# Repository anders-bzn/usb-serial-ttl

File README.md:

# usb-serial-ttl
Isolated USB to serial adapter, TTL 1.8/3.3V level. The IO voltage needs to be
supplied from the host.

Uses KiCad 8.0 and [kicad-jlcpcb-tools](https://github.com/Bouni/kicad-jlcpcb-tool3.3Vs)
plugin for creating fabrication files.

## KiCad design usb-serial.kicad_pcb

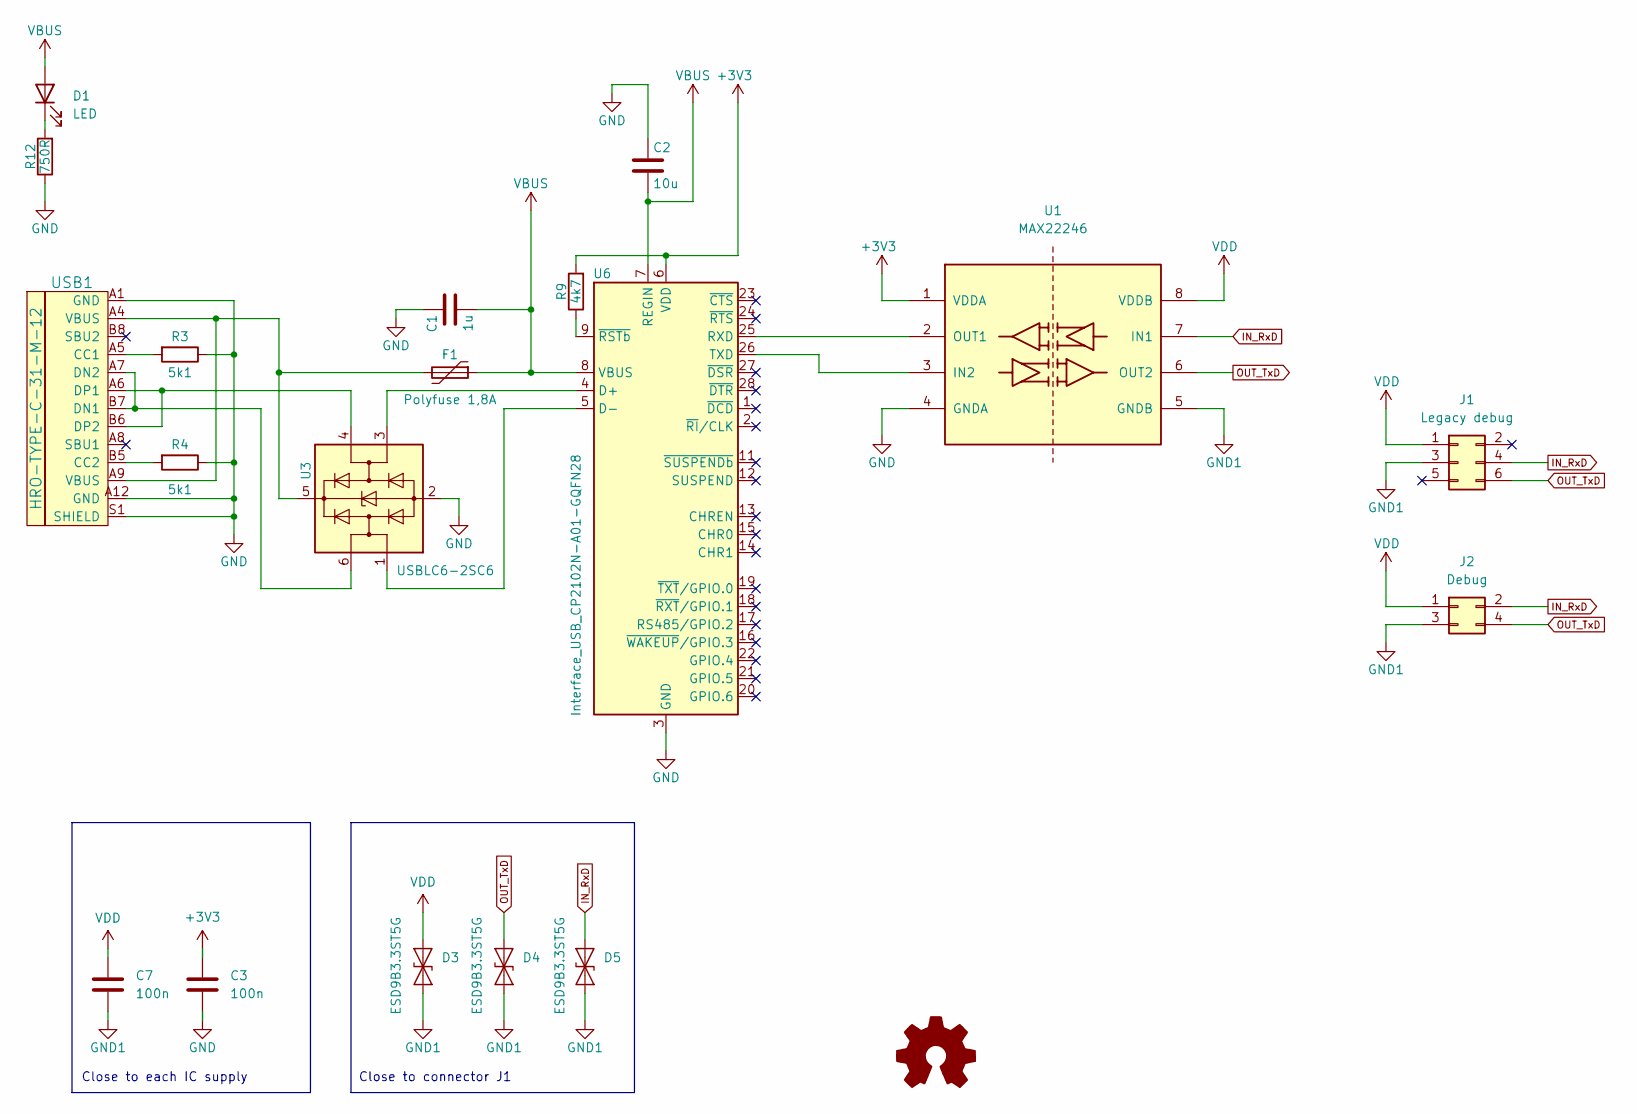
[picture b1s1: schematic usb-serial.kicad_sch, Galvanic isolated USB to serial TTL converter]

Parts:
C1: 1u; C_0805_2012Metric
C2: 10u; C_0805_2012Metric
C3, C7: 100n; C_0402_1005Metric
D1: LED; LED_0805_2012Metric
D3, D4, D5: ESD9B3.3ST5G; D_SOD-923
F1: Polyfuse 1,8A; Fuse_1206_3216Metric
J1: Legacy debug; PinHeader_2x03_P2.00mm_Vertical_SMD
J2: Debug; JST_PH_S4B-PH-SM4-TB_1x04-1MP_P2.00mm_Horizontal
R3, R4: 5k1; R_0402_1005Metric
R9: 4k7; R_0402_1005Metric
R12: 750R; R_0402_1005Metric
U1: MAX22246; SOP-8_5.28x5.23mm_P1.27mm
U3: USBLC6-2SC6; SOT-23-6
U6: Interface_USB_CP2102N-A01-GQFN28; QFN-28-1EP_5x5mm_P0.5mm_EP3.35x3.35mm
USB1: HRO-TYPE-C-31-M-12; USB_C_Receptacle_HRO_TYPE-C-31-M-12

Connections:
+3V3: C3.1, R9.2, U1.1 (VDDA), U6.6 (VDD)
GND: C1.1, C2.1, C3.2, R3.1, R4.1, R12.1, U1.4 (GNDA), U3.2 (GND), U6.3 (GND), U6.29 (GND), USB1.A1 (GND), USB1.A12 (GND), USB1.S1 (SHIELD)
GND1: C7.2, D3.1 (A1), D4.1 (A1), D5.1 (A1), J1.3, J2.3, U1.5 (GNDB)
IN_RxD: D5.2 (A2), J1.4, J2.2, U1.7 (IN1)
unnamed: D1.1 (K), R12.2
unnamed: U1.3 (IN2), U6.26 (TXD)
unnamed: U1.2 (OUT1), U6.25 (RXD)
unnamed: F1.2, U3.5 (VBUS), USB1.A4 (VBUS), USB1.A9 (VBUS)
unnamed: U3.3 (I/O2), U6.4 (D+)
unnamed: U3.1 (I/O1), U6.5 (D-)
unnamed: R9.1, U6.9 (~RSTb)
unnamed: R3.2, USB1.A5 (CC1)
unnamed: R4.2, USB1.B5 (CC2)
unnamed: U3.6 (I/O1), USB1.A7 (DN2), USB1.B7 (DN1)
unnamed: U3.4 (I/O2), USB1.A6 (DP1), USB1.B6 (DP2)
OUT_TxD: D4.2 (A2), J1.6, J2.4, U1.6 (OUT2)
VBUS: C1.2, C2.2, D1.2 (A), F1.1, U6.7 (REGIN), U6.8 (VBUS)
VDD: C7.1, D3.2 (A2), J1.1, J2.1, U1.8 (VDDB)

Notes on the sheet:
Close to each IC supply
Close to connector J1

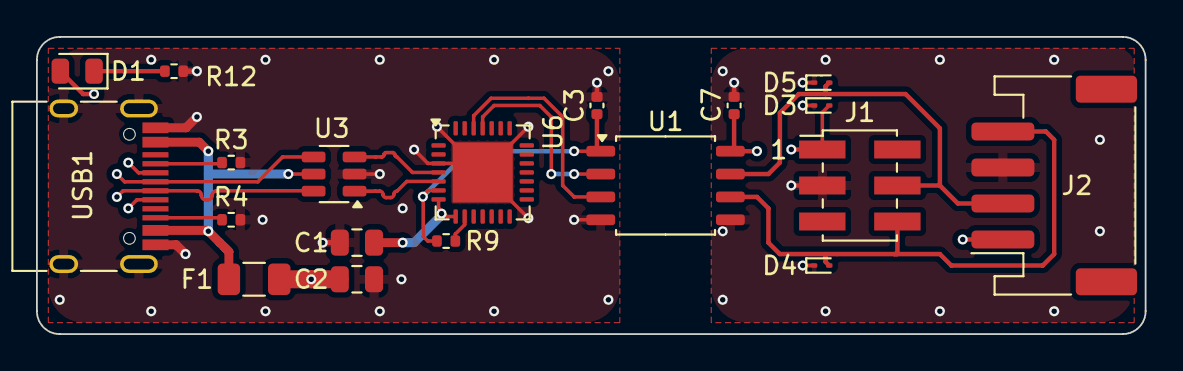
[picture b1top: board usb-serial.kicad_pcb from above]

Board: 4 copper layers, 61.6 x 16.5 mm, 19 parts (0 on the bottom side), 18 nets.

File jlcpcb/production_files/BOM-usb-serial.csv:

Comment,Designator,Footprint,LCSC,Quantity
4k7,R9,R_0402_1005Metric,C105870,1
5k1,"R3,R4",R_0402_1005Metric,C105872,2
10u,C2,C_0805_2012Metric,C15850,1
HRO-TYPE-C-31-M-12,USB1,USB_C_Receptacle_HRO_TYPE-C-31-M-12,C165948,1
Debug,J2,JST_PH_S4B-PH-SM4-TB_1x04-1MP_P2.00mm_Horizontal,C265102,1
1u,C1,C_0805_2012Metric,C28323,1
LED,D1,LED_0805_2012Metric,C2971980,1
100n,"C3,C7",C_0402_1005Metric,C307331,2
Legacy debug,J1,PinHeader_2x03_P2.00mm_Vertical_SMD,C32713241,1
"Polyfuse 1,8A",F1,Fuse_1206_3216Metric,C70081,1
USBLC6-2SC6,U3,SOT-23-6,C7519,1
750R,R12,R_0402_1005Metric,C881134,1
Interface_USB_CP2102N-A01-GQFN28,U6,QFN-28-1EP_5x5mm_P0.5mm_EP3.35x3.35mm,C964632,1
ESD9B3.3ST5G,"D3,D4,D5",D_SOD-923,C96512,3

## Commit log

2024-10-21 Add files
2024-10-21 README.md: Fix typo
2024-12-03 Change to capacitive isolator
2024-12-03 usb-serial.pdf: Regenerate
